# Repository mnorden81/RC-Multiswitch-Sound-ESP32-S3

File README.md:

# RC-Multiswitch-Sound-ESP32-S3

RC-Multiswitch mit 8 Kanaelen plus Soundmodul auf einem ESP32-S3-DevKitC-1.

Frueher `CRSF-Multiswitch-Sound-ESP32-S3`, umbenannt passend zu RC-Multiswitch-ESP32-C3 und -S3.

Kombiniert den RC-Multiswitch mit einem Soundmodul auf einer Platine: 8 Schaltkanaele ueber TBD62083APG (Nachfolger des ULN2803A) und Soundausgabe ueber I2S, Sounds von microSD. Ziel ist ein Modul fuer Modelle, die Licht und Sound zusammen brauchen.

Ausfuehrliche Projektbeschreibung: [docs/Projektbeschreibung.docx](docs/Projektbeschreibung.docx)

## Merkmale
- 8 Schaltkanaele ueber TBD62083APG, Kontroll-LED je Kanal
- UART A (Eingang), UART B und UART C als JST PH 4
- Audio: PCM5102A-DAC mit externem TPA3118-Verstaerker (HW-327, mono, aus VLOAD; Quelle mono: Kanal L direkt an den Verstaerker, kein Mono-Mix)
- microSD-Kartenmodul (6-polig) ueber SPI, Versorgung fest 3,3 V vom ESP32-Board (nur reine 3,3-V-Module verwenden)

## Hardware (v0.8, Entwurf, nur Schaltplan)
Board: ESP32-S3-DevKitC-1 N16R8 (oder Clone)

- Lastspannung 3S LiPo, 9-12,6 V (VLOAD) an CN2 (JST PH 2), TVS-Diode P6KE15A als Schutz.
- Treiber TBD62083APG (DMOS, Nachfolger des ULN2803A, gleiche Pinbelegung; ein ULN2803A passt weiterhin in den Sockel), 8 Kanaele, max. 500 mA je Kanal, Summe aller Kanaele ca. 1,5 A. Spannungsabfall am Ausgang nur ca. 0,2-0,4 V statt ca. 1 V beim ULN2803A.
- R9-R16 (THT 1/4 W) zwischen Treiber-Ausgang und Stiftleiste J1: Es ist kein Wert vorgegeben. Der Anwender muss die Widerstaende selbst passend zu Verbraucher und Lastspannung (3S, 9-12,6 V) auslegen, Strom und Verlustleistung beachten.
- R1-R8 und LED1-LED8 (3 mm) als Kontroll-LED je Kanal, vom Steuersignal Sn (3,3 V) gegen GND. Auch hier legt der Anwender die Werte selbst fest. Eine Empfehlung fuer die Kontroll-LEDs steht im Schaltplan.
- Keine Pulldowns und keine Widerstaende in den UART-Leitungen. Der ESP32 wird aus +5 V von CN1 (BEC/Empfaenger) versorgt.

### Belegung
| Funktion | GPIO |
|---|---|
| S0..S7 | IO4, IO5, IO6, IO7, IO15, IO16, IO1, IO2 |
| UART A (CN1, Eingang) | TX IO17, RX IO18 |
| UART B (J5) | TX IO39, RX IO40 |
| UART C (J6) | TX IO41, RX IO42 |
| SD (SPI) | CS IO10, MOSI IO11, SCK IO12, MISO IO13 |
| I2S | BCLK IO14, LRCK IO21, DOUT IO47 |

### Anschluesse
- CN1, J5, J6: UART A/B/C als JST PH 4 horizontal (S4B-PH-K)
- CN2 Last 3S LiPo (9-12,6 V) (JST PH 2), CN4 Lautsprecherausgang (JST PH 2, SPK+ / SPK-)
- J2 PCM5102A-Modul: Pin 1-6 = Stiftleiste (VIN, GND, LCK, DIN, BCK, SCK), Pin 7-10 = Ausgangspads G, R, G, L. Die Quelle ist mono: Pad L (Pin 10) und G (Pin 7, 9) gehen per Leiterbahn direkt an J11, Pad R (Pin 8) bleibt unbenutzt (No-Connect). Kein Mono-Mix, keine Mischwiderstaende.
- J11 TPA3118-Modul (HW-327), wird auf die Platine geloetet: Pad 1 IN, 2 GND, 3 PWR+ (VLOAD), 4 PWR- (GND), 5 OUT+ und 6 OUT- (zu CN4); die MUTE-Pads bleiben offen
- J9 microSD-Modul (6 Pins, VCC an 3V3 des ESP32-Boards, eigener Footprint mit Befestigungsloechern)

### Hinweise
- Gesperrte GPIOs: IO0/3/45/46 (Strapping), IO19/20 (USB), IO26-37 (Flash/PSRAM), IO43/44 (UART0). IO38/48 je nach Board an der RGB-LED.
- Footprint ESP32-S3-DevKitC-1_THT mit Reihenabstand 25,4 mm. Vor dem Layout am echten Board nachmessen. Eigene Footprints fuer PCM5102A, microSD-Modul und TPA3118-Modul liegen in hardware/footprints.pretty; die Masse sind aus Fotos geschaetzt und vor dem Layout nachzumessen.
- Nicht gleichzeitig USB und BEC anschliessen, ohne die Schutzdiode des Boards zu pruefen.

## Firmware (v1.03, nicht auf Hardware getestet)
Arduino-Sketch [firmware/RC_Multiswitch_Sound](firmware/RC_Multiswitch_Sound), Beschreibung in [firmware/README.md](firmware/README.md).

Reine Zusammenfuehrung von zwei bestehenden Firmwares:
- Schaltteil: RC-Multiswitch-ESP32-S3 v4.06 (= ESP32-Multiswitch-Basis V3/TXRX mit S3-Teilen): 8 Ausgaenge, Blinken, PWM, MWprop, bis 3 Konfigurationen je Ausgang, MKan-Gruppen, CRSF-Modulkette.
- Soundteil: ESP32-Sound-Basis_Ziege-One v7.21: Motor (start/loop/shut) und 24 Sounds von der SD-Karte, Upload der WAV-Dateien per WLAN.
- Gemeinsam: RC-System (CRSF oder SBUS auf UART A), WLAN und Web-UI, Lua-Menue am Sender, UART B/C (CRSF-Modulkette, S.Port, GPS, Raw), Firmware-Update per WLAN, Einstellungs-Backup im Flash und auf der SD-Karte.

Neu gegenueber den Basis-Firmwares (Entscheidungen 21.-28.10.2026):
- Zwei Adressen: Schalt-Adresse (Ausgaenge, zugleich CRSF-Geraeteadresse) und Sound-Adresse (Einzelkanal-Sounds). Gleiche Zahl = dieselben Schalter schalten beides.
- Status-LED in der Web-UI waehlbar: IO48 (DevKitC-1 v1.0, Vorgabe) oder IO38 (v1.1).
- Lua-Menue: Ordner zeigen ihren aktuellen Wert (z. B. „Ausgang 1 (Kanal_L 5)“, „Einstellungen (ELRS CRSF)“), Felder ohne Wirkung werden ausgeblendet (z. B. reine SBUS-Felder, Blinkzeiten bei Dauerlicht). Reihenfolge im Hauptmenü: Version, Global, Ausgang 1–8, WLAN, UART B/C, Motor, Einstellungen, Gerätename, Sound 1–n.
- Lua-Menue zeigt die ersten 8 Sounds, in der Web-UI auf bis zu 23 erhoehbar (Grenze: 255 Lua-Felder). In der Web-UI sind immer alle 24 Sounds einstellbar.
- Eigener Name je Sound und je Ausgang (16 Zeichen), Vorgabe "Sound N" bzw. "Ausgang N".

## Firmware flashen

Es gibt drei Wege. Ein neues Modul wird einmal per USB geflasht (Weg 1 oder Weg 2), danach geht jedes Update bequem per WLAN (Weg 3).

| Weg | Braucht | Einstellungen im Modul |
|---|---|---|
| 1. Fertige Datei aus GitHub + Web-Flasher | nur Chrome oder Edge | werden **gelöscht** |
| 2. Arduino IDE | Arduino IDE 2.x | bleiben erhalten |
| 3. Update per WLAN | Handy oder PC mit WLAN | bleiben erhalten |

### Weg 1: Fertige Firmware aus GitHub (ohne Arduino IDE)

GitHub baut die Firmware bei jeder Änderung automatisch (Workflow „Firmware bauen“).

1. Auf GitHub angemeldet sein (sonst gibt es keinen Download-Knopf).
2. In diesem Repo oben auf **Actions** klicken, links den Workflow **Firmware bauen** wählen.
3. Den obersten Lauf mit grünem Haken öffnen (Branch `main`).
4. Ganz unten unter **Artifacts** **RC_Multiswitch_Sound-S3** herunterladen und die ZIP-Datei entpacken. Darin liegen u. a. `RC_Multiswitch_Sound.ino.merged.bin` (Komplett-Image für USB) und `RC_Multiswitch_Sound.ino.bin` (nur für Weg 3).
   Steht dort nichts (Artefakte werden nach 90 Tagen gelöscht): rechts oben **Run workflow** → **Run workflow** klicken, nach ca. 3 Minuten ist ein neuer Lauf fertig.
5. ESP32-S3-DevKitC-1 mit einem USB-**Datenkabel** an den PC stecken (Buchse „USB“ oder „UART“, beide gehen). Für die Buchse „UART“ braucht Windows evtl. den Treiber für den USB-Seriell-Chip (CP210x oder CH343).
6. In **Chrome** oder **Edge** die Seite https://espressif.github.io/esptool-js/ öffnen (Espressif-Web-Flasher, Firefox geht nicht).
7. **Connect** klicken und den COM-Port des Moduls wählen. Klappt das nicht: Baudrate oben auf `115200` stellen und das Modul mit der BOOT-Taste in den Flash-Modus bringen (siehe Weg 2, „Wenn das Hochladen nicht klappt“).
8. Unter **Flash Address** `0x0` eintragen, mit **Datei auswählen** die `.merged.bin` wählen, dann **Program** klicken.
9. Wenn unten „Leaving…“ steht, das USB-Kabel kurz abziehen und wieder einstecken. Fertig.

> **Achtung:** Das Komplett-Image überschreibt den ganzen Flash (4 MB). Alle Einstellungen und die Sicherungen im Flash (die Sounds und Sicherungen auf der SD-Karte bleiben) sind danach weg. Vorher in der Weboberfläche die Einstellungen als Datei sichern (Schaltteil: Karte **Konfiguration sichern/wiederherstellen** → „Als Datei exportieren“, Soundteil: Karte **Konfiguration sichern / wiederherstellen** → „Export“ oder „Auf SD sichern“) und hinterher dort wieder importieren. Wer die Einstellungen behalten will, nimmt Weg 2 oder 3.

### Weg 2: Arduino IDE

**Einmalig einrichten**

1. Arduino IDE 2.x installieren (https://www.arduino.cc/en/software).
2. **Datei → Einstellungen → Zusätzliche Boardverwalter-URLs**: `https://espressif.github.io/arduino-esp32/package_esp32_index.json` eintragen.
3. **Werkzeuge → Board → Boardverwalter**: „esp32“ suchen, **esp32 von Espressif Systems** in Version **3.0.7 (in GitHub getestet; 3.3.12 geht auch)** installieren.
4. **Werkzeuge → Bibliotheken verwalten**: **Bolder Flight Systems SBUS 8.1.4**, **TinyGPSPlus 1.0.3** suchen und in genau dieser Version installieren.
   Alles andere (z. B. `src/RC_Common/`) liegt schon im Sketch-Ordner.

**Flashen**

1. Repo herunterladen: oben auf GitHub **Code → Download ZIP**, entpacken (oder den vorhandenen Ordner nehmen).
2. In der Arduino IDE **Datei → Öffnen** und `firmware/RC_Multiswitch_Sound/RC_Multiswitch_Sound.ino` wählen.
3. Unter **Werkzeuge** einstellen:

   | Einstellung | Wert |
   |---|---|
   | Board | **ESP32S3 Dev Module** |
   | USB CDC On Boot | **Enabled** |
   | USB Mode | **USB-OTG (TinyUSB)** (ab v1.04, für die SD-Karte als USB-Laufwerk; mit „Hardware CDC and JTAG“ läuft alles außer dem Laufwerk) |
   | Upload Mode | **USB-OTG CDC (TinyUSB)** (beim Hochladen über die Buchse „USB“) |
   | Flash Size | 4MB (32Mb) |
   | Partition Scheme | **Minimal SPIFFS (1.9MB APP with OTA/128KB SPIFFS)** |
   | PSRAM | **Disabled** |
   | Erase All Flash Before Sketch Upload | **Disabled** (sonst sind die Einstellungen weg) |

4. ESP32-S3-DevKitC-1 mit einem USB-**Datenkabel** an der Buchse **USB** an den PC stecken (die Buchse „UART“ geht auch, braucht aber evtl. den Treiber für den USB-Seriell-Chip CP210x oder CH343). Dann unter **Werkzeuge → Port** den neuen COM-Port wählen. Hinweis: Läuft die Firmware ab v1.04 (TinyUSB), bekommt das Modul eine andere COM-Port-Nummer als im Flash-Modus. Nach dem Hochladen also ggf. den Port neu wählen.
5. Auf den Pfeil **Hochladen** klicken. Am Ende steht „Hard resetting via RTS pin…“.
6. Das Modul startet von selbst neu. Wenn nicht: USB-Kabel kurz abziehen und wieder einstecken.

**Wenn das Hochladen nicht klappt** („Failed to connect“ oder „No serial data received“): Taste **BOOT** gedrückt halten, kurz **RST** drücken, BOOT loslassen. Das Board ist jetzt im Flash-Modus. Noch einmal **Hochladen**, danach einmal **RST** drücken.

### Weg 3: Update per WLAN (OTA)

1. Die Datei `RC_Multiswitch_Sound.ino.bin` besorgen: aus GitHub (Weg 1, Schritte 1–4) oder in der Arduino IDE mit **Sketch → Kompilierte Binärdatei exportieren** (liegt dann im Sketch-Ordner unter `build/`). Nicht die `.merged.bin` nehmen.
2. WLAN des Moduls einschalten: BOOT-Taste 3 s halten (oder Lua „WLAN jetzt“ bzw. automatisch ohne RC-Signal). Name **MultiSwitch**, Passwort `123456789` (falls nicht geändert).
3. Mit Handy oder PC in dieses WLAN gehen und im Browser http://192.168.1.1 öffnen.
4. Reiter **WiFi**, Karte **Firmware-Update (OTA)**: die `.bin`-Datei auswählen und hochladen. Das Modul startet danach neu, die Einstellungen bleiben erhalten.

Schlägt das Update fehl, läuft die alte Firmware einfach weiter. Das Modul beim Update am besten über den Empfänger/BEC versorgen, nicht nur über einen schwachen USB-Anschluss.

## Ordner
- `hardware/`: KiCad-Projekt (Schaltplan, PCB, PDF, eigene Footprints, fp-lib-table). Entwurfsnotizen in [hardware/README-hardware.md](hardware/README-hardware.md).
- `firmware/`: Firmware (Arduino-Sketch `RC_Multiswitch_Sound`), Build in GitHub Actions.
- `hardware/gehaeuse/`: 3D-Druck-Gehaeuse (STL, STEP, CadQuery-Quelle), siehe [hardware/gehaeuse/README.md](hardware/gehaeuse/README.md).
  - Zwei Versionen: J1 als stehende Stiftleiste (Kabel nach vorne/oben) oder als gewinkelte Stiftleiste 2x8, deren Stecker vorne durch die Wand kommen. 3D-Vorschau mit bestueckter Platine: `hardware/gehaeuse/Gehaeuse3D_Vorschau.html` und `hardware/gehaeuse/Gehaeuse3D_Vorschau_gewinkelt.html`.
- `docs/`: Projektbeschreibung als DOCX.

## Stand
- Hardware: Schaltplan v0.8, PCB in Arbeit. ERC-Stand v0.3 (hardware/ERC.rpt): 1 Fehler (IO8 unbeschaltet, seit v0.4 mit No-Connect-Flag, plus Rest-Leitungsstueck entfernt) und 55 Warnungen (Bibliotheksversionen "power"/"Device"/"local", harmlos). Nach v0.8 ERC neu ausfuehren.
- Firmware: v1.05 (Multiswitch V3 + Sound-Basis v7.21, Lua-Fix Kanalwahl aus v7.22, SD-Karte als USB-Laufwerk, übersichtlicheres Lua-Menü), baut in GitHub Actions, auf Hardware noch nicht getestet.

## Offene Punkte
- R1-R16 vom Anwender je LED bzw. Verbraucher auslegen (3S, ca. 11-12 V); Helligkeit schwankt mit dem Ladezustand.
- Schaltplan v0.8 im PCB per F8 (Aktualisieren aus Schaltplan) uebernehmen: J10, R18, R19, J3, J4, R17, J7, J8 entfallen (Footprints ohne Symbol loeschen lassen), J2, J9 und J11 bekommen die neuen Modul-Footprints (J11 jetzt TPA3118 mit 6 Pads), CN3 entfaellt, CN4 (Lautsprecher) ist neu. hardware/*.pdf ist noch der Stand v0.1.
- ERC mit v0.8 neu ausfuehren; Symbolbibliothek "local" einbinden (reduziert die Warnungen).
- TPA3118-Modul (HW-327): Modul-Mindestspannung 8 V beachten (3S-Akku nicht unter ca. 9 V entladen, Abschaltung ueber Fahrregler/Unterspannungswaechter), MUTE-Header offen, Leiterbahnbreite und Stromaufnahme gegen CN2/CN4 (JST PH, ca. 2 A je Kontakt) pruefen.
- microSD-Modul muss ein reines 3,3-V-Modul sein (Standard-Module mit Spannungsregler bekommen sonst zu wenig Spannung); Pinreihenfolge am Modul gegen J9 (VCC, CS, MOSI, SCK, MISO, GND) pruefen.
- Module nachmessen und Footprints anpassen: PCM5102A, microSD-Modul, TPA3118 (Padlage, Befestigungsloecher, Belegung IN/GND per Multimeter pruefen), ESP32-S3-DevKitC-1.
- PCB-Layout erstellen
- Gehaeuse (hardware/gehaeuse/) am echten Aufbau pruefen: Hoehe Elko C1 (22 mm angenommen), ESP 13 mm ueber der Platine, Lage USB-C und microSD-Slot
- Firmware v1.03 auf der Platine testen (Ausgaenge, Sound, SD-Karte, Status-LED IO48/IO38)

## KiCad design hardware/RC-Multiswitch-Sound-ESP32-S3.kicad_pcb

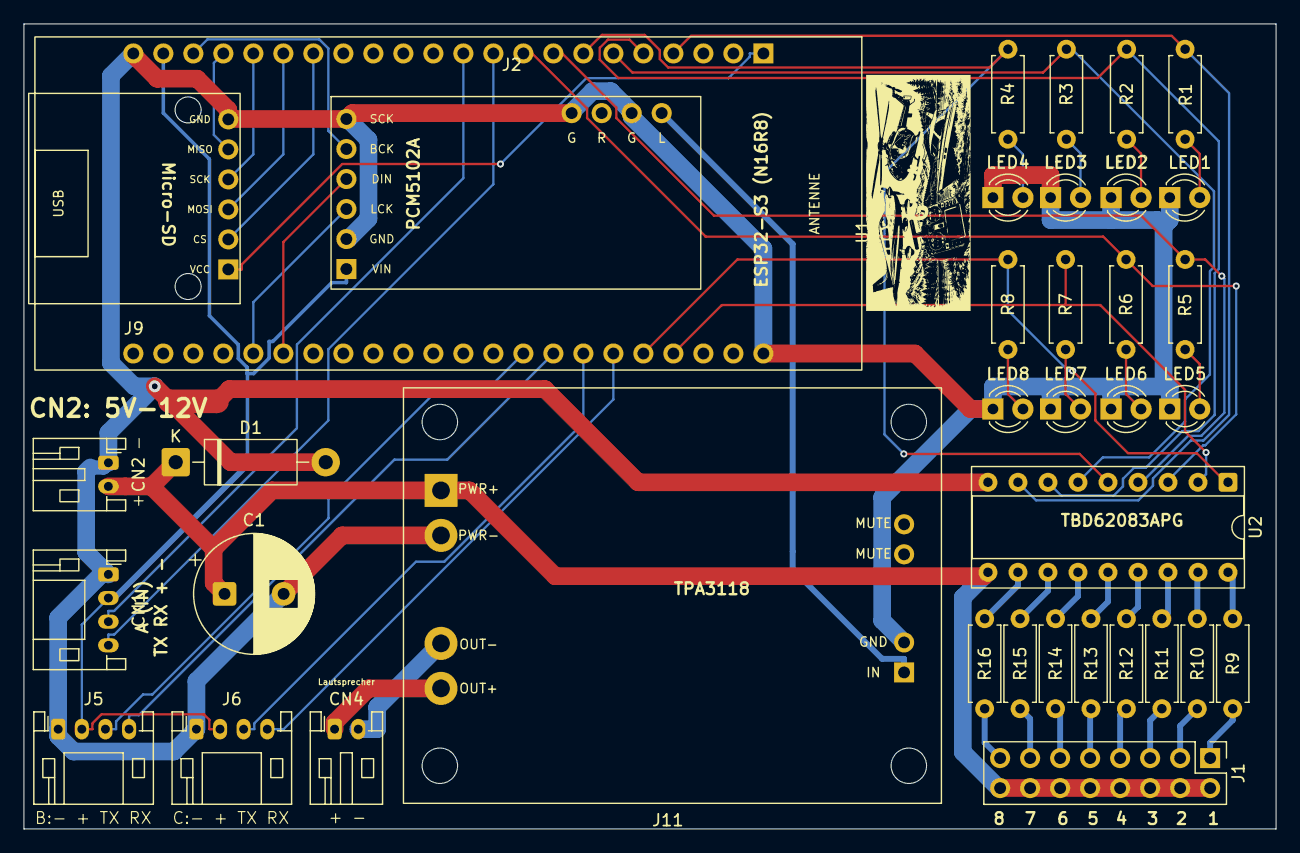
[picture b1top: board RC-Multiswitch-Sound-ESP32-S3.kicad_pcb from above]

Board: 2 copper layers, 106.0 x 68.2 mm, 38 parts (0 on the bottom side), 53 nets.

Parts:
C1: 470u/35V; CP_Radial_D10.0mm_P5.00mm
CN1: UART A; JST_PH_S4B-PH-K_1x04_P2.00mm_Horizontal
CN2: 3S; JST_PH_S2B-PH-K_1x02_P2.00mm_Horizontal
CN4: Lautsprecher; JST_PH_S2B-PH-K_1x02_P2.00mm_Horizontal
D1: P6KE15A; D_DO-15_P12.70mm_Horizontal
J1: Ausgaenge; PinHeader_2x08_P2.54mm_Vertical
J2: PCM5102A; Mod_PCM5102A_GY_THT
J5: UART B; JST_PH_S4B-PH-K_1x04_P2.00mm_Horizontal
J6: UART C; JST_PH_S4B-PH-K_1x04_P2.00mm_Horizontal
J9: microSD-TF-Modul; Mod_microSD_SPI_THT
J11: TPA3118 HW-327; Mod_TPA3118_HW327_THT
LED1, LED2, LED3, LED4, LED5, LED6, LED7, LED8: LED; LED_D3.0mm
NT1: NetTie GND/GNDPWR; NetTie-2_SMD_Pad2.0mm
R1, R2, R3, R4, R5, R6, R7, R8, R9, R10, R11, R12, R13, R14, R15, R16: R; R_Axial_DIN0207_L6.3mm_D2.5mm_P7.62mm_Horizontal
U1: ESP32-S3-DevKitC-1 (N16R8); ESP32-S3-DevKitC-1_THT
U2: TBD62083APG; DIP-18_W7.62mm_Socket

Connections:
+3V3: J9.1 (VCC), U1.1 (3V3)
+5V: CN1.2 (+5V), J2.1 (VIN), J5.2 (+5V), J6.2 (+5V), U1.21 (5V)
/AUDIO_MONO: J2.10 (L), J11.1 (IN)
/I2S_BCLK: J2.5 (BCK), U1.20 (IO14)
/I2S_DOUT: J2.4 (DIN), U1.39 (IO47)
/I2S_LRCK: J2.3 (LCK), U1.40 (IO21)
/OUT1: R9.1, U2.18 (O1)
/OUT1L: J1.1 (OUT1), R9.2
/OUT2: R10.1, U2.17 (O2)
/OUT2L: J1.3 (OUT2), R10.2
/OUT3: R11.1, U2.16 (O3)
/OUT3L: J1.5 (OUT3), R11.2
/OUT4: R12.1, U2.15 (O4)
/OUT4L: J1.7 (OUT4), R12.2
/OUT5: R13.1, U2.14 (O5)
/OUT5L: J1.9 (OUT5), R13.2
/OUT6: R14.1, U2.13 (O6)
/OUT6L: J1.11 (OUT6), R14.2
/OUT7: R15.1, U2.12 (O7)
/OUT7L: J1.13 (OUT7), R15.2
/OUT8: R16.1, U2.11 (O8)
/OUT8L: J1.15 (OUT8), R16.2
/S0: R1.1, U1.4 (IO4), U2.8 (I8)
/S1: R2.1, U1.5 (IO5), U2.7 (I7)
/S2: R3.1, U1.6 (IO6), U2.6 (I6)
/S3: R4.1, U1.7 (IO7), U2.5 (I5)
/S4: R5.1, U1.8 (IO15), U2.4 (I4)
/S5: R6.1, U1.9 (IO16), U2.3 (I3)
/S6: R7.1, U1.26 (IO1), U2.2 (I2)
/S7: R8.1, U1.27 (IO2), U2.1 (I1)
/SD_CS: J9.2 (CS), U1.16 (IO10)
/SD_MISO: J9.5 (MISO), U1.19 (IO13)
/SD_MOSI: J9.3 (MOSI), U1.17 (IO11)
/SD_SCK: J9.4 (SCK), U1.18 (IO12)
/UA_RX: CN1.3 (RX), U1.11 (IO18)
/UA_TX: CN1.4 (TX), U1.10 (IO17)
/UB_RX: J5.4 (RX), U1.30 (IO40)
/UB_TX: J5.3 (TX), U1.31 (IO39)
/UC_RX: J6.4 (RX), U1.28 (IO42)
/UC_TX: J6.3 (TX), U1.29 (IO41)
/VLOAD: C1.1, CN2.2 (V+), D1.1 (K), J1.2 (V+), J1.4 (V+), J1.6 (V+), J1.8 (V+), J1.10 (V+), J1.12 (V+), J1.14 (V+), J1.16 (V+), J11.3 (PWR+), U2.10 (COM)
GND: C1.2, CN1.1 (GND), CN2.1 (GND), D1.2 (A), J2.2 (GND), J2.6 (SCK), J2.7 (AGND), J2.9 (AGND), J5.1 (GND), J6.1 (GND), J9.6 (GND), J11.2 (GND), J11.4 (PWR-), LED1.1 (K), LED2.1 (K), LED3.1 (K), LED4.1 (K), LED5.1 (K), LED6.1 (K), LED7.1 (K), LED8.1 (K), NT1.1, U1.22 (GND), U1.23 (GND)
GNDPWR: NT1.2, U2.9 (GND)
unnamed: CN4.1 (SPK+), J11.5 (OUT+)
unnamed: CN4.2 (SPK-), J11.6 (OUT-)
unnamed: LED1.2 (A), R1.2
unnamed: LED2.2 (A), R2.2
unnamed: LED3.2 (A), R3.2
unnamed: LED4.2 (A), R4.2
unnamed: LED5.2 (A), R5.2
unnamed: LED6.2 (A), R6.2
unnamed: LED7.2 (A), R7.2
unnamed: LED8.2 (A), R8.2

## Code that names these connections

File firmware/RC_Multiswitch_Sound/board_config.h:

/*
 * board_config.h  -  Pin- und Board-Konfiguration RC-Multiswitch-Sound v1.00
 *
 * Platine RC-Multiswitch-Sound-ESP32-S3 v0.9 mit ESP32-S3-DevKitC-1 N16R8
 * (oder Clone). Pinbelegung laut README.md (Abschnitt "Belegung") und
 * hardware/RC-Multiswitch-Sound-ESP32-S3.kicad_sch.
 *
 * Arduino-IDE-Einstellungen:
 *   Board:            ESP32S3 Dev Module
 *   USB CDC On Boot:  Enabled  (Debug-Ausgaben ueber USB, UART0 = UART A)
 *   Partition Scheme: Minimal SPIFFS (1.9MB APP with OTA/128KB SPIFFS)
 *                     (OTA-Update per WLAN + Einstellungs-Backup im Flash)
 *   PSRAM:            Disabled (wird nicht gebraucht)
 */
#pragma once
#include <Arduino.h>

#if !defined(CONFIG_IDF_TARGET_ESP32S3)
  #error "Bitte Board 'ESP32S3 Dev Module' waehlen"
#endif

#if !ARDUINO_USB_CDC_ON_BOOT
  #error "Bitte 'USB CDC On Boot: Enabled' einstellen - UART0 wird fuer UART A (CRSF/SBUS) gebraucht"
#endif

#define BOARD_S3
#define BOARD_NAME "S3 Kombi"

// Ausgaenge S0..S7 (Kanal 1..8), alle mit LEDC-Kanal
static constexpr uint8_t OutPin[8] = {4, 5, 6, 7, 15, 16, 1, 2};
static constexpr bool    OutPwm[8] = {true, true, true, true, true, true, true, true};

// UART A (CN1, Eingang vom Empfaenger) = UART0, CRSF oder SBUS
#define UART_A_SERIAL Serial0
static constexpr uint8_t UART_A_RX = 18;
static constexpr uint8_t UART_A_TX = 17;
// UART B (J5) = UART1
#define UART_B_SERIAL Serial1
static constexpr uint8_t UART_B_RX = 40;
static constexpr uint8_t UART_B_TX = 39;
// UART C (J6) = UART2
#define UART_C_SERIAL Serial2
static constexpr uint8_t UART_C_RX = 42;
static constexpr uint8_t UART_C_TX = 41;

// microSD (J9) ueber SPI
static constexpr uint8_t SD_CS   = 10;
static constexpr uint8_t SD_MOSI = 11;
static constexpr uint8_t SD_SCK  = 12;
static constexpr uint8_t SD_MISO = 13;

// I2S zum PCM5102A (J2), mono: der Verstaerker haengt am Kanal L
static constexpr uint8_t I2S_BCLK = 14;
static constexpr uint8_t I2S_LRC  = 21;
static constexpr uint8_t I2S_DOUT = 47;

static constexpr uint8_t BOOT_BTN_PIN = 0;

// RGB-LED (WS2812) des DevKitC-1: v1.0 an IO48, v1.1 an IO38. Der Pin wird
// in der Web-UI gewaehlt (NVS "ledpin", wirkt nach einem Neustart).
static constexpr int STATUS_LED_PIN_DEFAULT = 48;
static constexpr int STATUS_LED_PIN_ALT     = 38;
#define STATUS_LED_WS2812 1
static constexpr uint8_t STATUS_LED_BRIGHTNESS = 40;  // von 255, ca. 15 %
